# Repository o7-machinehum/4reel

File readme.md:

# 4reel
4reel is a platform for robots that don't have enough computing power to run machine vision algorithms. It's capable of stereo depth processing, image classification and SLAM.

When connected over USB-C the device will present itself as an Ethernet adapter and DHCP you an IP address, configuration can be done on the web portal at `http://192.168.77.1:8080/`

The JST connecter can be used to send data UART to an Arduino, ESP32, etc. The same JST conncetor can be used to power the device with 5V.

## System Overview

## Repo structure
``` bash
.
|-- img
|-- os
|-- readme.md
|-- ref
|-- rv1103    # Current tested board
|-- rv1106    # Next generation
`-- scripts   # Automation scripts I wrote
```

# Media
- https://youtube.com/shorts/XkLzl0wEfN4?si=KPXePSXCayTTsI1j

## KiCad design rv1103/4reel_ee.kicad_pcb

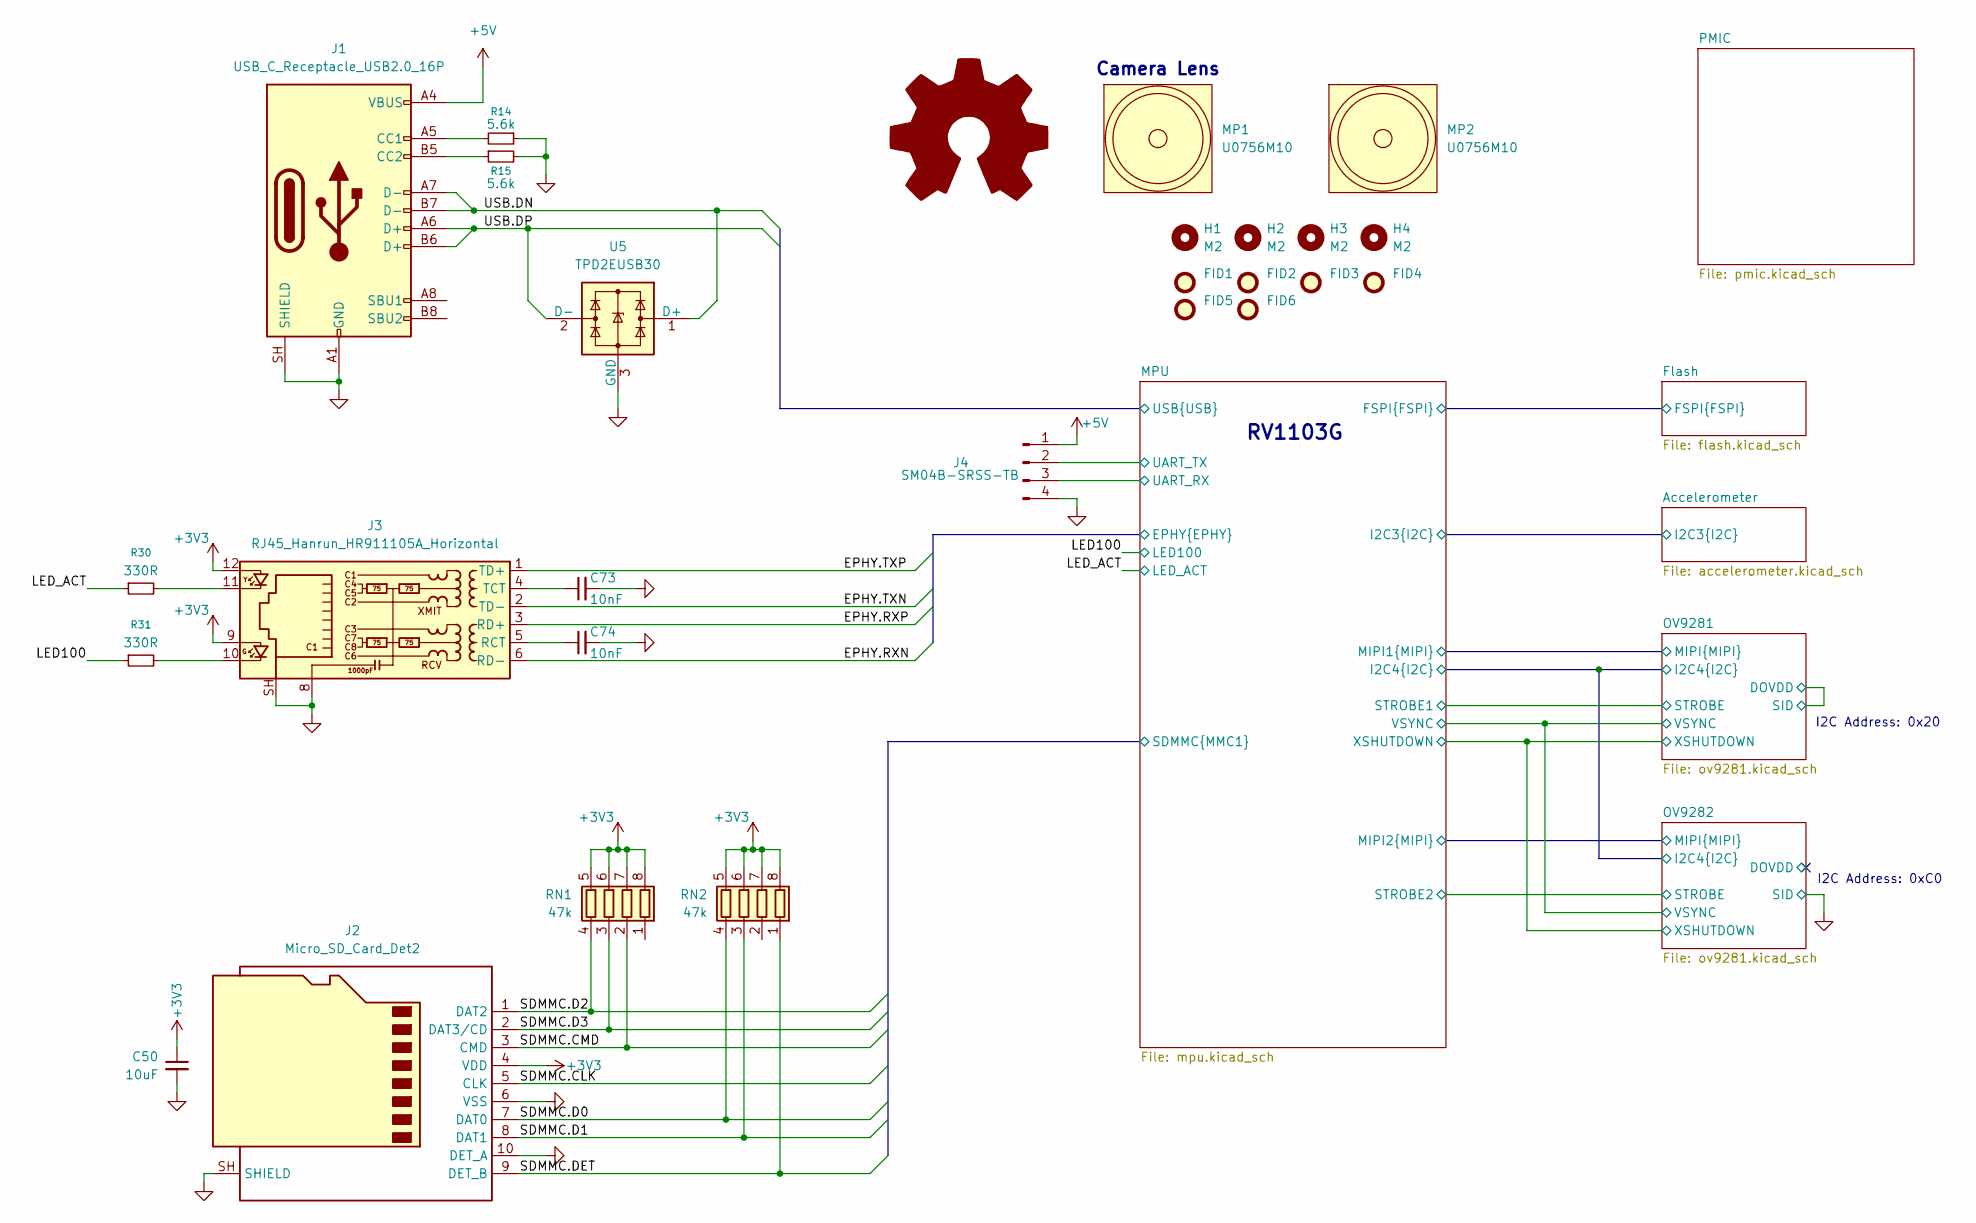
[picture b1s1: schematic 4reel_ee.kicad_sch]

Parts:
C50: 10uF; C_0402_1005Metric; MPN GRM155R60J106ME05D
C73, C74: 10nF; C_0402_1005Metric; MPN C0402C103K5REC7411
FID1, FID2, FID3, FID4, FID5, FID6: Fiducial; Fiducial_0.5mm_Mask1.5mm
H1, H2, H3, H4: M2; MountingHole_2.2mm_M2
J1: USB_C_Receptacle_USB2.0_16P; USB_C_Receptacle_GCT_USB4105-xx-A_16P_TopMnt_Horizontal; MPN USB4105-GF-A-120
J2: Micro_SD_Card_Det2; microSD_HC_Hirose_DM3AT-SF-PEJM5; MPN DM3AT-SF-PEJM5
J3: RJ45_Hanrun_HR911105A_Horizontal; MPN HR911105A
J4: SM04B-SRSS-TB; JST_SH_SM04B-SRSS-TB_1x04-1MP_P1.00mm_Horizontal; MPN SM04B-SRSS-TB
MP1, MP2: Camera_Lens_20mm; MPN U0756M10
R14, R15: 5.6k; R_0402_1005Metric; MPN RC0402FR-075K6L
R30, R31: 330R; R_0402_1005Metric; MPN RC0402FR-07330RL
RN1, RN2: 47k; R_Array_Concave_4x0402; MPN CAT10-473J4LF
SYM1: Logo_Open_Hardware_Large; OSHW-Logo2_14.6x12mm_SilkScreen
U5: TPD2EUSB30; Texas_DRT-3; MPN TPD2EUSB30ADRTR

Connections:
+3V3: C50.1, J2.4 (VDD), J3.9, J3.12, RN1.5 (R4.2), RN1.6 (R3.2), RN1.7 (R2.2), RN1.8 (R1.2), RN2.5 (R4.2), RN2.6 (R3.2), RN2.7 (R2.2), RN2.8 (R1.2); also elsewhere on the board
+5V: J1.A4 (VBUS), J1.A9 (VBUS), J1.B4 (VBUS), J1.B9 (VBUS), J4.1; also elsewhere on the board
/LED100: R31.1; also elsewhere on the board
/LED_ACT: R30.1; also elsewhere on the board
/MPU/EPHY.RXN: J3.6 (RD-); also elsewhere on the board
/MPU/EPHY.RXP: J3.3 (RD+); also elsewhere on the board
/MPU/EPHY.TXN: J3.2 (TD-); also elsewhere on the board
/MPU/EPHY.TXP: J3.1 (TD+); also elsewhere on the board
/MPU/SDMMC.CLK: J2.5 (CLK); also elsewhere on the board
/MPU/SDMMC.CMD: J2.3 (CMD), RN1.2 (R2.1); also elsewhere on the board
/MPU/SDMMC.D0: J2.7 (DAT0), RN2.4 (R4.1); also elsewhere on the board
/MPU/SDMMC.D1: J2.8 (DAT1), RN2.3 (R3.1); also elsewhere on the board
/MPU/SDMMC.D2: J2.1 (DAT2), RN1.4 (R4.1); also elsewhere on the board
/MPU/SDMMC.D3: J2.2 (DAT3/CD), RN1.3 (R3.1); also elsewhere on the board
/MPU/SDMMC.DET: J2.9 (DET_B), RN2.1 (R1.1); also elsewhere on the board
/MPU/UART_RX: J4.3; also elsewhere on the board
/MPU/UART_TX: J4.2; also elsewhere on the board
/MPU/USB.DN: J1.A7 (D-), J1.B7 (D-), U5.1 (D+); also elsewhere on the board
/MPU/USB.DP: J1.A6 (D+), J1.B6 (D+), U5.2 (D-); also elsewhere on the board
GND: C50.2, C73.2, C74.2, J1.A1 (GND), J1.A12 (GND), J1.B1 (GND), J1.B12 (GND), J1.SH (SHIELD), J2.6 (VSS), J2.10 (DET_A), J2.SH (SHIELD), J3.8, J3.SH, J4.4, R14.1, R15.2, U5.3 (GND); also elsewhere on the board
unnamed: J1.A5 (CC1), R14.2
unnamed: J1.B5 (CC2), R15.1
unnamed: J3.10, R31.2
unnamed: J3.11, R30.2
unnamed: C74.1, J3.5 (RCT)
unnamed: C73.1, J3.4 (TCT)

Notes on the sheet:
Camera Lens
I2C Address: 0x20
I2C Address: 0xC0
RV1103G

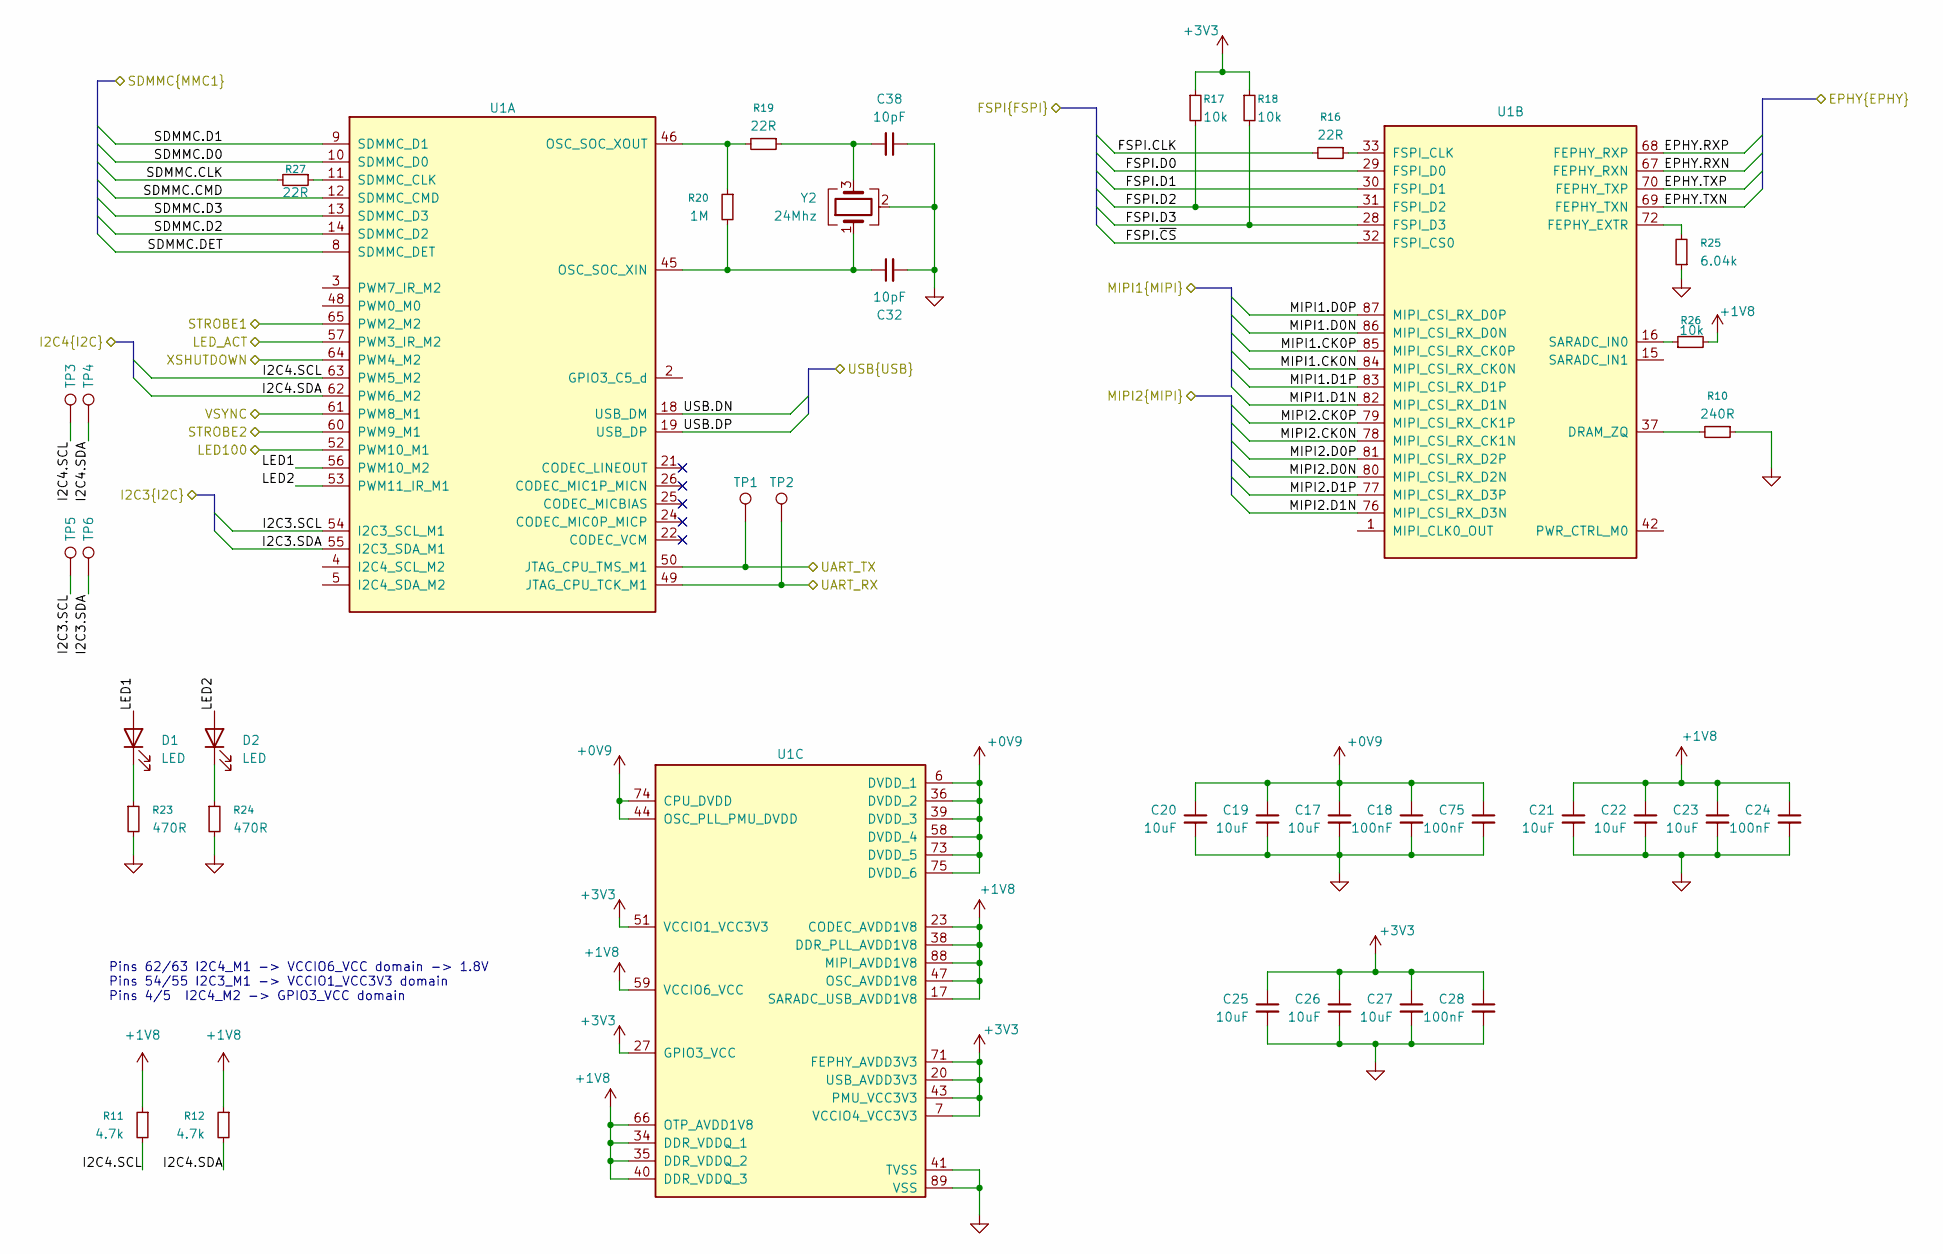
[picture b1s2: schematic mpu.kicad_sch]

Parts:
C17, C19, C20, C21, C22, C23, C25, C26, C27: 10uF; C_0402_1005Metric; MPN GRM155R60J106ME05D
C18, C24, C28, C75: 100nF; C_0402_1005Metric; MPN CL05B104KP5VPNC
C32, C38: 10pF; C_0402_1005Metric; MPN GCM1555C1H100JA16D
D1, D2: LED; LED_0402_1005Metric; MPN LTST-C281KGKT
R10: 240R; R_0402_1005Metric; MPN RC0402FR-07240RL
R11, R12: 4.7k; R_0402_1005Metric; MPN RC0402FR-074K7L
R16, R19: 22R; R_0402_1005Metric; MPN RC0402FR-0722RL
R17, R18, R26: 10k; R_0402_1005Metric; MPN RC0402FR-0710KL
R20: 1M; R_0402_1005Metric; MPN RC0402FR-071ML
R23, R24: 470R; R_0402_1005Metric; MPN RC0402FR-07470RL
R25: 6.04k; R_0402_1005Metric; MPN RC0402FR-076K04L
R27: 22R; R_0201_0603Metric; MPN RC0201FR-0722RL
TP1, TP2: TestPoint; TestPoint_Pad_1.5x1.5mm
TP3, TP4, TP5, TP6: TestPoint; TestPoint_Pad_1.0x1.0mm
U1: RV1103G; Rockchip_QFN-88-1EP_9x9mm_P0.35mm_EP6.5x6.5mm; MPN RV1103G1
Y2: 24Mhz; Crystal_SMD_2016-4Pin_2.0x1.6mm; MPN ECS-240-8-37B-CKY-TR

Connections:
+0V9: C17.1, C18.1, C19.1, C20.1, C75.1, U1.6 (DVDD_1), U1.36 (DVDD_2), U1.39 (DVDD_3), U1.44 (OSC_PLL_PMU_DVDD), U1.58 (DVDD_4), U1.73 (DVDD_5), U1.74 (CPU_DVDD), U1.75 (DVDD_6); also elsewhere on the board
+1V8: C21.1, C22.1, C23.1, C24.1, R11.1, R12.1, R26.2, U1.17 (SARADC_USB_AVDD1V8), U1.23 (CODEC_AVDD1V8), U1.34 (DDR_VDDQ_1), U1.35 (DDR_VDDQ_2), U1.38 (DDR_PLL_AVDD1V8), U1.40 (DDR_VDDQ_3), U1.47 (OSC_AVDD1V8), U1.59 (VCCIO6_VCC), U1.66 (OTP_AVDD1V8), U1.88 (MIPI_AVDD1V8); also elsewhere on the board
+3V3: C25.1, C26.1, C27.1, C28.1, R17.1, R18.1, U1.7 (VCCIO4_VCC3V3), U1.20 (USB_AVDD3V3), U1.27 (GPIO3_VCC), U1.43 (PMU_VCC3V3), U1.51 (VCCIO1_VCC3V3), U1.71 (FEPHY_AVDD3V3); also elsewhere on the board
/Accelerometer/I2C3.SCL: TP5.1 (1_1), U1.54 (I2C3_SCL_M1); also elsewhere on the board
/Accelerometer/I2C3.SDA: TP6.1 (1_1), U1.55 (I2C3_SDA_M1); also elsewhere on the board
/Flash/FSPI.CLK: R16.2; also elsewhere on the board
/Flash/FSPI.D0: U1.29 (FSPI_D0); also elsewhere on the board
/Flash/FSPI.D1: U1.30 (FSPI_D1); also elsewhere on the board
/Flash/FSPI.D2: R17.2, U1.31 (FSPI_D2); also elsewhere on the board
/Flash/FSPI.D3: R18.2, U1.28 (FSPI_D3); also elsewhere on the board
/Flash/FSPI.~CS: U1.32 (FSPI_CS0); also elsewhere on the board
/LED100: U1.52 (PWM10_M1); also elsewhere on the board
/LED_ACT: U1.57 (PWM3_IR_M2); also elsewhere on the board
/MPU/EPHY.RXN: U1.67 (FEPHY_RXN); also elsewhere on the board
/MPU/EPHY.RXP: U1.68 (FEPHY_RXP); also elsewhere on the board
/MPU/EPHY.TXN: U1.69 (FEPHY_TXN); also elsewhere on the board
/MPU/EPHY.TXP: U1.70 (FEPHY_TXP); also elsewhere on the board
/MPU/I2C4.SCL: R11.2, TP3.1 (1_1), U1.63 (PWM5_M2); also elsewhere on the board
/MPU/I2C4.SDA: R12.2, TP4.1 (1_1), U1.62 (PWM6_M2); also elsewhere on the board
/MPU/LED1: D1.2 (A), U1.56 (PWM10_M2)
/MPU/LED2: D2.2 (A), U1.53 (PWM11_IR_M1)
/MPU/MIPI1.CK0N: U1.84 (MIPI_CSI_RX_CK0N); also elsewhere on the board
/MPU/MIPI1.CK0P: U1.85 (MIPI_CSI_RX_CK0P); also elsewhere on the board
/MPU/MIPI1.D0N: U1.86 (MIPI_CSI_RX_D0N); also elsewhere on the board
/MPU/MIPI1.D0P: U1.87 (MIPI_CSI_RX_D0P); also elsewhere on the board
/MPU/MIPI1.D1N: U1.82 (MIPI_CSI_RX_D1N); also elsewhere on the board
/MPU/MIPI1.D1P: U1.83 (MIPI_CSI_RX_D1P); also elsewhere on the board
/MPU/MIPI2.CK0N: U1.78 (MIPI_CSI_RX_CK1N); also elsewhere on the board
/MPU/MIPI2.CK0P: U1.79 (MIPI_CSI_RX_CK1P); also elsewhere on the board
/MPU/MIPI2.D0N: U1.80 (MIPI_CSI_RX_D2N); also elsewhere on the board
/MPU/MIPI2.D0P: U1.81 (MIPI_CSI_RX_D2P); also elsewhere on the board
/MPU/MIPI2.D1N: U1.76 (MIPI_CSI_RX_D3N); also elsewhere on the board
/MPU/MIPI2.D1P: U1.77 (MIPI_CSI_RX_D3P); also elsewhere on the board
/MPU/SDMMC.CLK: R27.2; also elsewhere on the board
/MPU/SDMMC.CMD: U1.12 (SDMMC_CMD); also elsewhere on the board
/MPU/SDMMC.D0: U1.10 (SDMMC_D0); also elsewhere on the board
/MPU/SDMMC.D1: U1.9 (SDMMC_D1); also elsewhere on the board
/MPU/SDMMC.D2: U1.14 (SDMMC_D2); also elsewhere on the board
/MPU/SDMMC.D3: U1.13 (SDMMC_D3); also elsewhere on the board
/MPU/SDMMC.DET: U1.8 (SDMMC_DET); also elsewhere on the board
/MPU/STROBE1: U1.65 (PWM2_M2); also elsewhere on the board
/MPU/STROBE2: U1.60 (PWM9_M1); also elsewhere on the board
/MPU/UART_RX: TP2.1 (1_1), U1.49 (JTAG_CPU_TCK_M1); also elsewhere on the board
/MPU/UART_TX: TP1.1 (1_1), U1.50 (JTAG_CPU_TMS_M1); also elsewhere on the board
/MPU/USB.DN: U1.18 (USB_DM); also elsewhere on the board
/MPU/USB.DP: U1.19 (USB_DP); also elsewhere on the board
/MPU/VSYNC: U1.61 (PWM8_M1); also elsewhere on the board
/MPU/XSHUTDOWN: U1.64 (PWM4_M2); also elsewhere on the board
GND: C17.2, C18.2, C19.2, C20.2, C21.2, C22.2, C23.2, C24.2, C25.2, C26.2, C27.2, C28.2, C32.2, C38.1, C75.2, R10.1, R23.2, R24.2, R25.1, U1.41 (TVSS), U1.89 (VSS), Y2.2 (G), Y2.4 (G); also elsewhere on the board
unnamed: C38.2, R19.1, Y2.3
unnamed: D1.1 (K), R23.1
unnamed: D2.1 (K), R24.1
unnamed: R10.2, U1.37 (DRAM_ZQ)
unnamed: R25.2, U1.72 (FEPHY_EXTR)
unnamed: R16.1, U1.33 (FSPI_CLK)
unnamed: R26.1, U1.16 (SARADC_IN0)
unnamed: C32.1, R20.2, U1.45 (OSC_SOC_XIN), Y2.1
unnamed: R19.2, R20.1, U1.46 (OSC_SOC_XOUT)
unnamed: R27.1, U1.11 (SDMMC_CLK)

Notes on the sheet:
Pins 62/63 I2C4_M1 -> VCCIO6_VCC domain -> 1.8V Pins 54/55 I2C3_M1 -> VCCIO1_VCC3V3 domain Pins 4/5 I2C4_M2 -> GPIO3_VCC domain

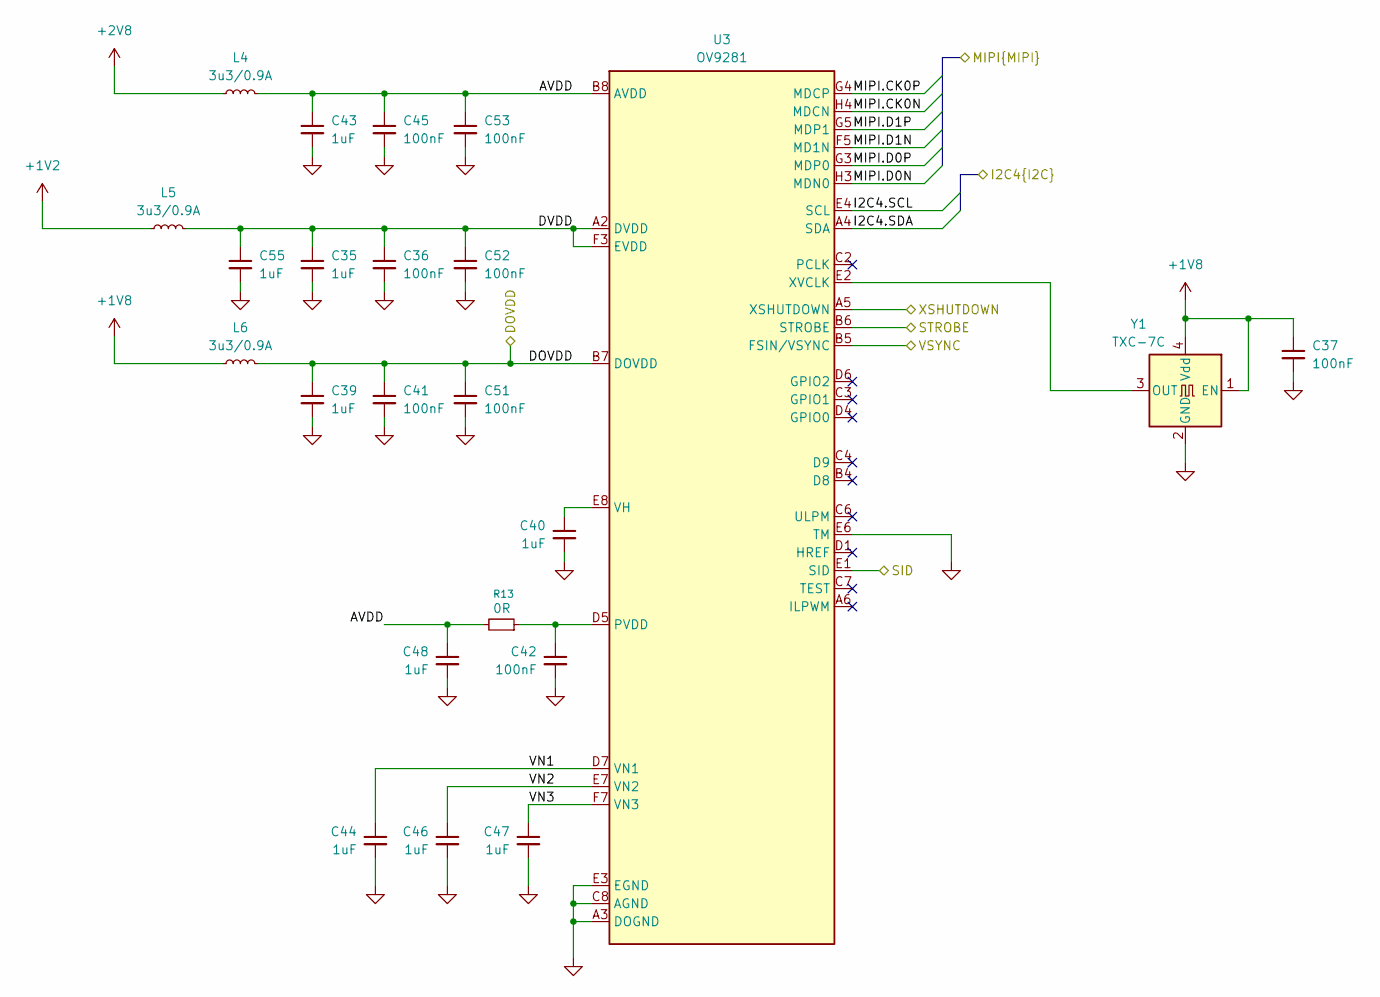
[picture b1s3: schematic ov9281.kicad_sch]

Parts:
C35, C39, C40, C43, C44, C46, C47, C48, C55: 1uF; C_0402_1005Metric; MPN C0402C105K9PACTU
C36, C37, C41, C42, C45, C51, C52, C53: 100nF; C_0402_1005Metric; MPN CL05B104KP5VPNC
L4, L5, L6: 3u3/0.9A; L_0805_2012Metric; MPN MLP2012S3R3MT0S1
R13: 0R; R_0402_1005Metric; MPN RC0402FR-070RL
U3: ImageSensor_OV9281; OV9281; MPN OV9281
Y1: TXC-7C; Oscillator_SMD_TXC_7C-4Pin_5.0x3.2mm; MPN SX5M24.000D20F30TNN

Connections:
+1V2: L5.1; also elsewhere on the board
+1V8: C37.1, L6.1, Y1.1 (EN), Y1.4 (Vdd); also elsewhere on the board
+2V8: L4.1; also elsewhere on the board
/MPU/I2C4.SCL: U3.E4 (SCL); also elsewhere on the board
/MPU/I2C4.SDA: U3.A4 (SDA); also elsewhere on the board
/MPU/MIPI1.CK0N: U3.H4 (MDCN); also elsewhere on the board
/MPU/MIPI1.CK0P: U3.G4 (MDCP); also elsewhere on the board
/MPU/MIPI1.D0N: U3.H3 (MDN0); also elsewhere on the board
/MPU/MIPI1.D0P: U3.G3 (MDP0); also elsewhere on the board
/MPU/MIPI1.D1N: U3.F5 (MD1N); also elsewhere on the board
/MPU/MIPI1.D1P: U3.G5 (MDP1); also elsewhere on the board
/MPU/STROBE1: U3.B6 (STROBE); also elsewhere on the board
/MPU/VSYNC: U3.B5 (FSIN/VSYNC); also elsewhere on the board
/MPU/XSHUTDOWN: U3.A5 (XSHUTDOWN); also elsewhere on the board
/OV9281/AVDD: C43.1, C45.1, C48.1, C53.1, L4.2, R13.2, U3.B8 (AVDD), U3.C1 (AVDD), U3.G7 (AVDD), U3.G8 (AVDD)
/OV9281/DOVDD: C39.1, C41.1, C51.1, L6.2, U3.B7 (DOVDD), U3.D3 (DOVDD), U3.E1 (SID), U3.H2 (DOVDD), U3.H6 (DOVDD)
/OV9281/DVDD: C35.1, C36.1, C52.1, C55.1, L5.2, U3.A2 (DVDD), U3.B1 (DVDD), U3.B3 (DVDD), U3.C5 (DVDD), U3.D8 (DVDD), U3.F2 (DVDD), U3.F3 (EVDD), U3.G1 (DVDD), U3.G6 (DVDD), U3.H5 (EVDD)
/OV9281/VN1: C44.1, U3.D7 (VN1)
/OV9281/VN2: C46.1, U3.E7 (VN2)
/OV9281/VN3: C47.1, U3.F7 (VN3)
GND: C35.2, C36.2, C37.2, C39.2, C40.2, C41.2, C42.2, C43.2, C44.2, C45.2, C46.2, C47.2, C48.2, C51.2, C52.2, C53.2, C55.2, U3.A3 (DOGND), U3.A7 (DOGND), U3.B2 (DOGND), U3.C8 (AGND), U3.D2 (AGND), U3.E3 (EGND), U3.E5 (EGND), U3.E6 (TM), U3.F1 (DOGND), U3.F4 (DOGND), U3.F6 (DOGND), U3.F8 (AGND), U3.G2 (DOGND), U3.H7 (AGND), Y1.2 (GND); also elsewhere on the board
unnamed: C42.1, R13.1, U3.D5 (PVDD)
unnamed: C40.1, U3.E8 (VH)
unnamed: U3.E2 (XVCLK), Y1.3 (OUT)

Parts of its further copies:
C56, C57, C58, C59, C60, C64, C65, C69, C71: 1uF; C_0402_1005Metric; MPN C0402C105K9PACTU
C61, C62, C63, C66, C67, C68, C70, C72: 100nF; C_0402_1005Metric; MPN CL05B104KP5VPNC
L7, L8, L9: 3u3/0.9A; L_0805_2012Metric; MPN MLP2012S3R3MT0S1
R32: 0R; R_0402_1005Metric; MPN RC0402FR-070RL
U9: ImageSensor_OV9281; OV9281; MPN OV9281
Y3: TXC-7C; Oscillator_SMD_TXC_7C-4Pin_5.0x3.2mm; MPN SX5M24.000D20F30TNN

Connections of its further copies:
+1V2: L7.1; also elsewhere on the board
+1V8: C72.1, L9.1, Y3.1 (EN), Y3.4 (Vdd); also elsewhere on the board
+2V8: L8.1; also elsewhere on the board
/MPU/I2C4.SCL: U9.E4 (SCL); also elsewhere on the board
/MPU/I2C4.SDA: U9.A4 (SDA); also elsewhere on the board
/MPU/MIPI2.CK0N: U9.H4 (MDCN); also elsewhere on the board
/MPU/MIPI2.CK0P: U9.G4 (MDCP); also elsewhere on the board
/MPU/MIPI2.D0N: U9.H3 (MDN0); also elsewhere on the board
/MPU/MIPI2.D0P: U9.G3 (MDP0); also elsewhere on the board
/MPU/MIPI2.D1N: U9.F5 (MD1N); also elsewhere on the board
/MPU/MIPI2.D1P: U9.G5 (MDP1); also elsewhere on the board
/MPU/STROBE2: U9.B6 (STROBE); also elsewhere on the board
/MPU/VSYNC: U9.B5 (FSIN/VSYNC); also elsewhere on the board
/MPU/XSHUTDOWN: U9.A5 (XSHUTDOWN); also elsewhere on the board
/OV9282/AVDD: C57.1, C61.1, C64.1, C66.1, L8.2, R32.2, U9.B8 (AVDD), U9.C1 (AVDD), U9.G7 (AVDD), U9.G8 (AVDD)
/OV9282/DOVDD: C59.1, C63.1, C68.1, L9.2, U9.B7 (DOVDD), U9.D3 (DOVDD), U9.H2 (DOVDD), U9.H6 (DOVDD)
/OV9282/DVDD: C56.1, C58.1, C62.1, C67.1, L7.2, U9.A2 (DVDD), U9.B1 (DVDD), U9.B3 (DVDD), U9.C5 (DVDD), U9.D8 (DVDD), U9.F2 (DVDD), U9.F3 (EVDD), U9.G1 (DVDD), U9.G6 (DVDD), U9.H5 (EVDD)
/OV9282/VN1: C60.1, U9.D7 (VN1)
/OV9282/VN2: C65.1, U9.E7 (VN2)
/OV9282/VN3: C69.1, U9.F7 (VN3)
GND: C56.2, C57.2, C58.2, C59.2, C60.2, C61.2, C62.2, C63.2, C64.2, C65.2, C66.2, C67.2, C68.2, C69.2, C70.2, C71.2, C72.2, U9.A3 (DOGND), U9.A7 (DOGND), U9.B2 (DOGND), U9.C8 (AGND), U9.D2 (AGND), U9.E1 (SID), U9.E3 (EGND), U9.E5 (EGND), U9.E6 (TM), U9.F1 (DOGND), U9.F4 (DOGND), U9.F6 (DOGND), U9.F8 (AGND), U9.G2 (DOGND), U9.H7 (AGND), Y3.2 (GND); also elsewhere on the board
unnamed: C70.1, R32.1, U9.D5 (PVDD)
unnamed: C71.1, U9.E8 (VH)
unnamed: U9.E2 (XVCLK), Y3.3 (OUT)

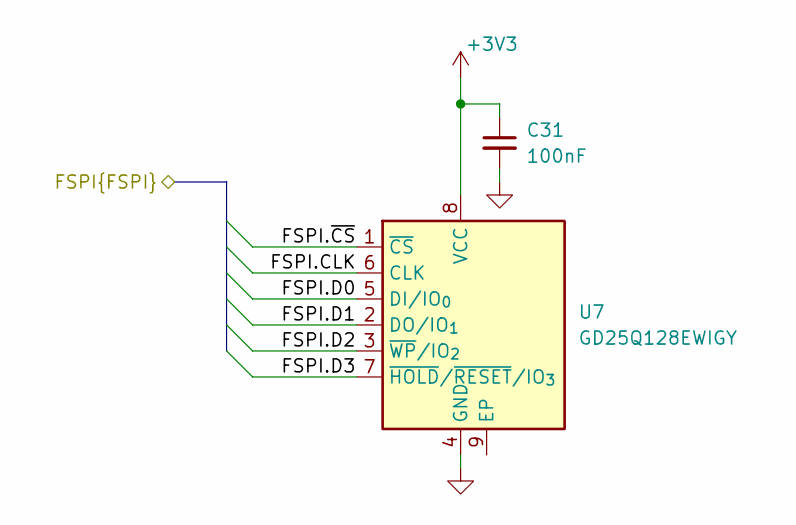
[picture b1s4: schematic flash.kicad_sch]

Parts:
C31: 100nF; C_0402_1005Metric; MPN CL05B104KP5VPNC
U7: GD25Q128EWIGY; WSON-8-1EP_6x5mm_P1.27mm_EP3.4x4.3mm; MPN GD25Q128EWIGY

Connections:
+3V3: C31.1, U7.8 (VCC); also elsewhere on the board
/Flash/FSPI.CLK: U7.6 (CLK); also elsewhere on the board
/Flash/FSPI.D0: U7.5 (DI/IO_{0}); also elsewhere on the board
/Flash/FSPI.D1: U7.2 (DO/IO_{1}); also elsewhere on the board
/Flash/FSPI.D2: U7.3 (~WP/IO_{2}); also elsewhere on the board
/Flash/FSPI.D3: U7.7 (~HOLD/~RESET/IO_{3}); also elsewhere on the board
/Flash/FSPI.~CS: U7.1 (~CS); also elsewhere on the board
GND: C31.2, U7.4 (GND); also elsewhere on the board

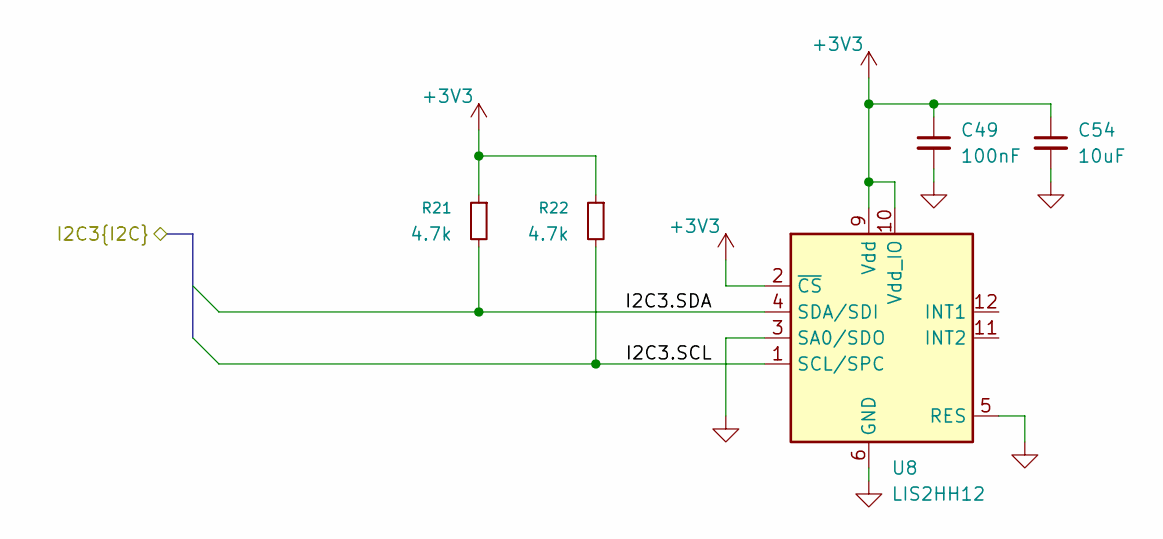
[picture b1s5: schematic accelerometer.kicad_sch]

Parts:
C49: 100nF; C_0402_1005Metric; MPN CL05B104KP5VPNC
C54: 10uF; C_0402_1005Metric; MPN GRM155R60J106ME05D
R21, R22: 4.7k; R_0402_1005Metric; MPN RC0402FR-074K7L
U8: LIS2HH12; LGA-12_2x2mm_P0.5mm; MPN LIS2HH12TR

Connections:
+3V3: C49.1, C54.1, R21.1, R22.1, U8.2 (~CS), U8.9 (Vdd), U8.10 (Vdd_IO); also elsewhere on the board
/Accelerometer/I2C3.SCL: R22.2, U8.1 (SCL/SPC); also elsewhere on the board
/Accelerometer/I2C3.SDA: R21.2, U8.4 (SDA/SDI); also elsewhere on the board
GND: C49.2, C54.2, U8.3 (SA0/SDO), U8.5 (RES), U8.6 (GND), U8.7 (GND), U8.8 (GND); also elsewhere on the board

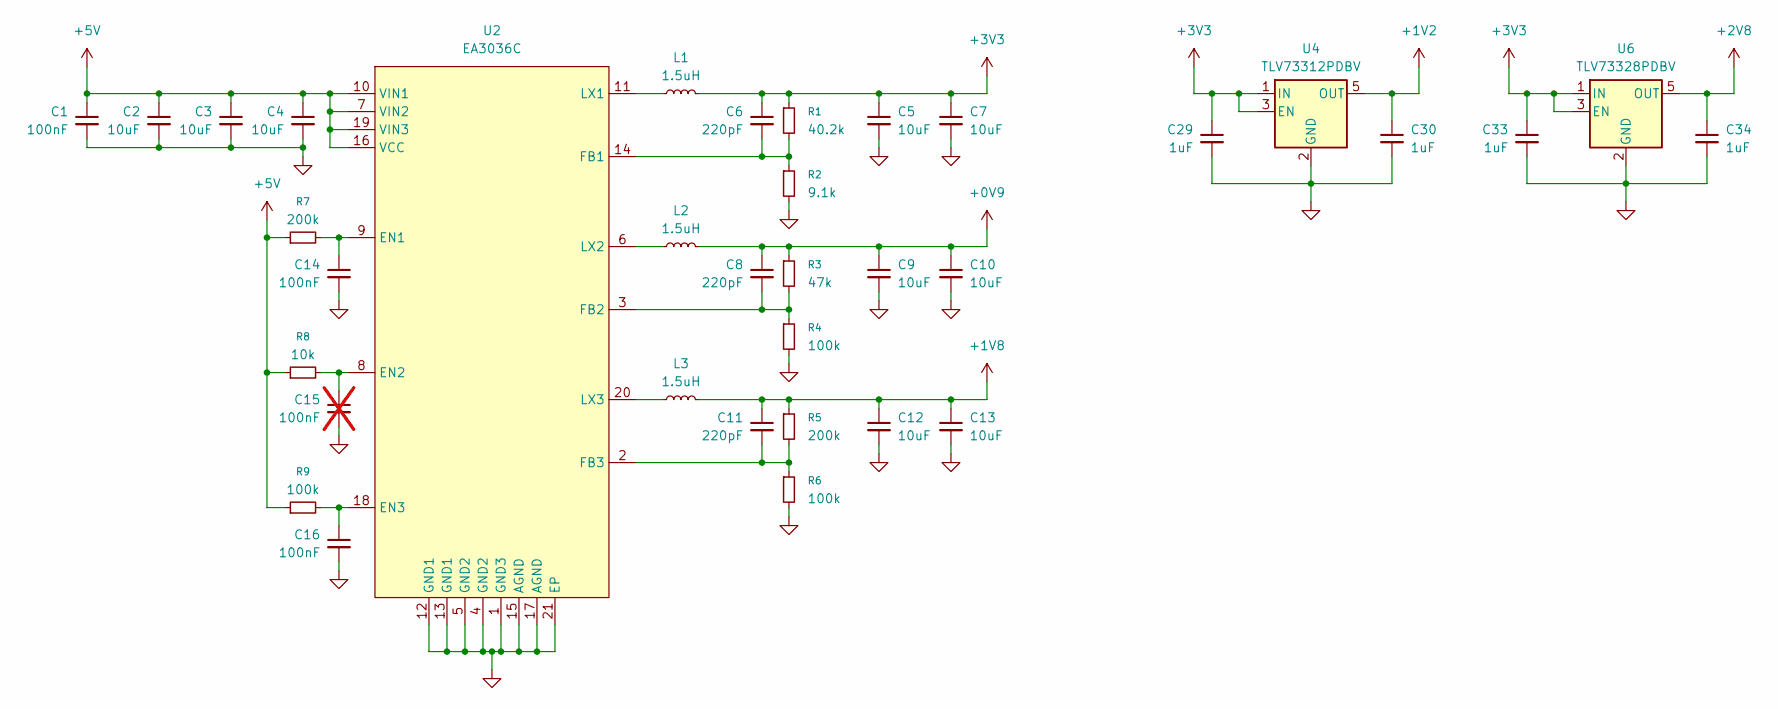
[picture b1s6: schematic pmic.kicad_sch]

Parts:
C1, C14, C16: 100nF; C_0402_1005Metric; MPN CL05B104KP5VPNC
C2, C3, C4, C5, C7, C9, C10, C12, C13: 10uF; C_0402_1005Metric; MPN GRM155R60J106ME05D
C6, C8, C11: 220pF; C_0402_1005Metric; MPN GCM1555C1H221JA16D
C15: 100nF; C_0402_1005Metric; MPN CL05B104KP5VPNC; not fitted
C29, C30, C33, C34: 1uF; C_0402_1005Metric; MPN C0402C105K9PACTU
L1, L2, L3: 1.5uH; L_1008_2520Metric; MPN DFE252012P-1R5M=P2
R1: 40.2k; R_0402_1005Metric; MPN RC0402FR-0740K2L
R2: 9.1k; R_0402_1005Metric; MPN RC0402FR-079K1L
R3: 47k; R_0402_1005Metric; MPN RC0402FR-0747KL
R4, R6, R9: 100k; R_0402_1005Metric; MPN RC0402FR-07100KL
R5, R7: 200k; R_0402_1005Metric; MPN RC0402FR-07200KL
R8: 10k; R_0402_1005Metric; MPN RC0402FR-0710KL
U2: EA3036C; QFN-20-1EP_3x3mm_P0.4mm_EP1.65x1.65mm; MPN EA3036CQBR
U4: TLV73312PDBV; SOT-23-5; MPN TLV73312PDBV
U6: TLV73328PDBV; SOT-23-5; MPN TLV73328PDBVR

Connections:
+0V9: C8.1, C9.1, C10.1, L2.2, R3.1; also elsewhere on the board
+1V2: C30.1, U4.5 (OUT); also elsewhere on the board
+1V8: C11.1, C12.1, C13.1, L3.2, R5.1; also elsewhere on the board
+2V8: C34.1, U6.5 (OUT); also elsewhere on the board
+3V3: C5.1, C6.1, C7.1, C29.1, C33.1, L1.2, R1.1, U4.1 (IN), U4.3 (EN), U6.1 (IN), U6.3 (EN); also elsewhere on the board
+5V: C1.1, C2.1, C3.1, C4.1, R7.1, R8.1, R9.1, U2.7 (VIN2), U2.10 (VIN1), U2.16 (VCC), U2.19 (VIN3); also elsewhere on the board
GND: C1.2, C2.2, C3.2, C4.2, C5.2, C7.2, C9.2, C10.2, C12.2, C13.2, C14.2, C15.2, C16.2, C29.2, C30.2, C33.2, C34.2, R2.2, R4.2, R6.2, U2.1 (GND3), U2.4 (GND2), U2.5 (GND2), U2.12 (GND1), U2.13 (GND1), U2.15 (AGND), U2.17 (AGND), U2.21 (EP), U4.2 (GND), U6.2 (GND); also elsewhere on the board
unnamed: C14.1, R7.2, U2.9 (EN1)
unnamed: C15.1, R8.2, U2.8 (EN2)
unnamed: C16.1, R9.2, U2.18 (EN3)
unnamed: C6.2, R1.2, R2.1, U2.14 (FB1)
unnamed: C8.2, R3.2, R4.1, U2.3 (FB2)
unnamed: C11.2, R5.2, R6.1, U2.2 (FB3)
unnamed: L1.1, U2.11 (LX1)
unnamed: L2.1, U2.6 (LX2)
unnamed: L3.1, U2.20 (LX3)

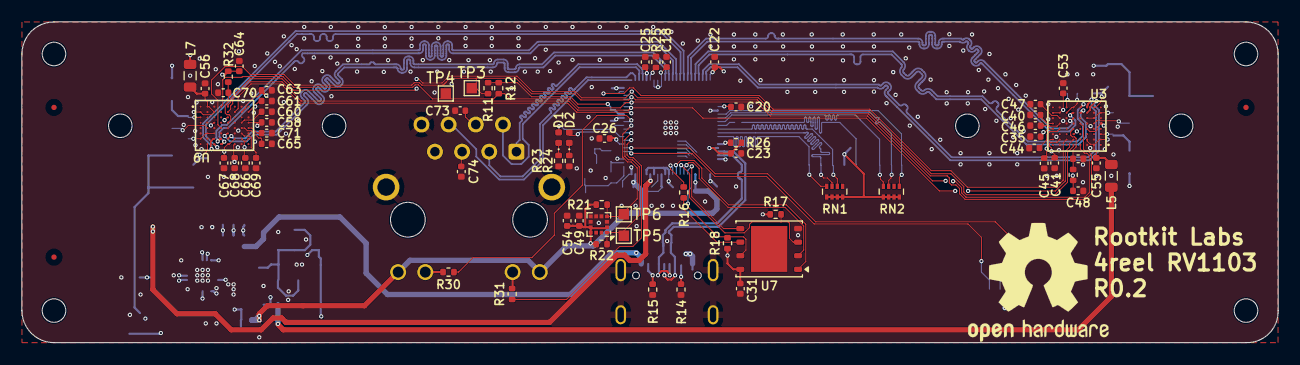
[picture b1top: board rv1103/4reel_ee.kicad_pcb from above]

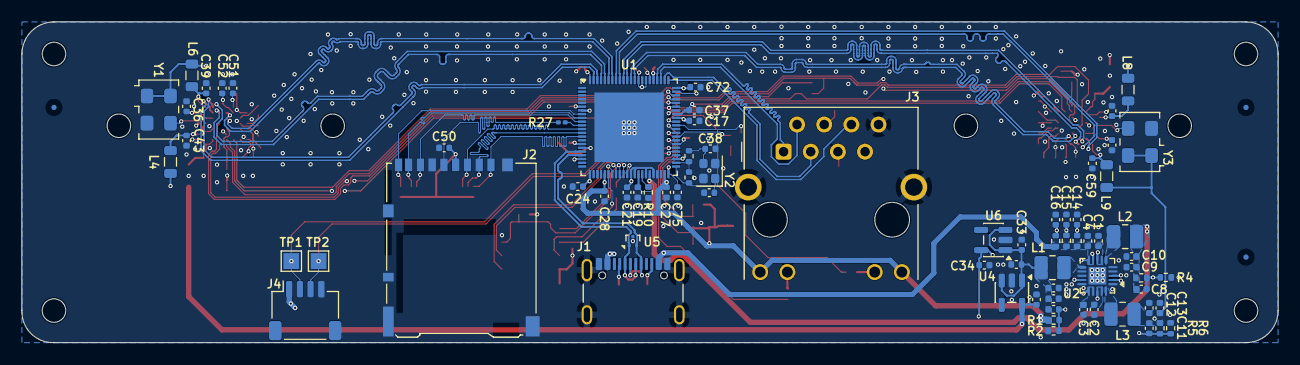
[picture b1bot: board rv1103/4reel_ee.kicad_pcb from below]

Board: 4 copper layers, 117.5 x 30.0 mm, 153 parts (77 on the bottom side), 95 nets.

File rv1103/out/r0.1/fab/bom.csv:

"Designator","Value","Footprint","Quantity","Part Number"
"C1,C14,C16,C18,C24,C28,C31,C36,C37,C41,C42,C45,C49,C51-C53,C61-C63,C66-C68,C70,C72,C75","100nF","Capacitor_SMD:C_0402_1005Metric","25","CL05B104KP5VPNC"
"C2-C5,C7,C9,C10,C12,C13,C17,C19-C23,C25-C27,C50,C54","10uF","Capacitor_SMD:C_0402_1005Metric","20","GRM155R60J106ME05D"
"C6,C8,C11","220pF","Capacitor_SMD:C_0402_1005Metric","3","GCM1555C1H221JA16D"
"C29,C30,C33-C35,C39,C40,C43,C44,C46-C48,C55-C60,C64,C65,C69,C71","1uF","Capacitor_SMD:C_0402_1005Metric","22","C0402C105K9PACTU"
"C32,C38","10pF","Capacitor_SMD:C_0402_1005Metric","2","GCM1555C1H100JA16D"
"C73,C74","10nF","Capacitor_SMD:C_0402_1005Metric","2","C0402C103K5REC7411"
"D1,D2","LED","LED_SMD:LED_0402_1005Metric","2","LTST-C281KGKT"
"J1","USB_C_Receptacle_USB2.0_16P","Connector_USB:USB_C_Receptacle_GCT_USB4105-xx-A_16P_TopMnt_Horizontal","1","USB4105-GF-A-120"
"J2","Micro_SD_Card_Det2","Connector_Card:microSD_HC_Hirose_DM3AT-SF-PEJM5","1","DM3AT-SF-PEJM5"
"J3","RJ45_Hanrun_HR911105A_Horizontal","Connector_RJ:RJ45_Hanrun_HR911105A_Horizontal","1","HR911105A"
"J4","JST","Connector_JST:JST_SH_SM04B-SRSS-TB_1x04-1MP_P1.00mm_Horizontal","1","SM04B-SRSS-TB"
"L1-L3","1.5uH","Inductor_SMD:L_1008_2520Metric","3","DFE252012P-1R5M=P2"
"L4-L9","3u3/0.9A","Inductor_SMD:L_0805_2012Metric","6","MLP2012S3R3MT0S1"
"R1","40.2k","Resistor_SMD:R_0402_1005Metric","1","RC0402FR-0740K2L"
"R2","9.1k","Resistor_SMD:R_0402_1005Metric","1","RC0402FR-079K1L"
"R3","47k","Resistor_SMD:R_0402_1005Metric","1","RC0402FR-0747KL"
"R4,R6,R9","100k","Resistor_SMD:R_0402_1005Metric","3","RC0402FR-07100KL"
"R5,R7","200k","Resistor_SMD:R_0402_1005Metric","2","RC0402FR-07200KL"
"R8,R17,R18,R26","10k","Resistor_SMD:R_0402_1005Metric","4","RC0402FR-0710KL"
"R10","240R","Resistor_SMD:R_0402_1005Metric","1","RC0402FR-07240RL"
"R11,R12,R21,R22","4.7k","Resistor_SMD:R_0402_1005Metric","4","RC0402FR-074K7L"
"R13,R32","0R","Resistor_SMD:R_0402_1005Metric","2","RC0402FR-070RL"
"R14,R15","5.6k","Resistor_SMD:R_0402_1005Metric","2","RC0402FR-075K6L"
"R16,R19","22R","Resistor_SMD:R_0402_1005Metric","2","RC0402FR-0722RL"
"R20","1M","Resistor_SMD:R_0402_1005Metric","1","RC0402FR-071ML"
"R23,R24","1k","Resistor_SMD:R_0402_1005Metric","2","RC0402FR-071KL"
"R25","6.04k","Resistor_SMD:R_0402_1005Metric","1","RC0402FR-076K04L"
"R27","22R","Resistor_SMD:R_0201_0603Metric","1","RC0201FR-0722RL"
"R30,R31","330R","Resistor_SMD:R_0402_1005Metric","2","RC0402FR-07330RL"
"RN1,RN2","47k","Resistor_SMD:R_Array_Concave_4x0402","2","CAT10-473J4LF"
"TP3-TP6","TestPoint","TestPoint:TestPoint_Pad_1.0x1.0mm","4",""
"U1","RV1103G","rv1103b:Rockchip_QFN-88-1EP_9x9mm_P0.35mm_EP6.5x6.5mm","1","RV1103BG3"
"U2","EA3036C","Package_DFN_QFN:QFN-20-1EP_3x3mm_P0.4mm_EP1.65x1.65mm","1","EA3036CQBR"
"U3,U9","ImageSensor_OV9281","ov9281:OV9281","2","OV9281"
"U4","TLV73312PDBV","Package_TO_SOT_SMD:SOT-23-5","1","TLV73312PDBV"
"U5","TPD2EUSB30","Package_TO_SOT_SMD:Texas_DRT-3","1","TPD2EUSB30ADRTR"
"U6","TLV73328PDBV","Package_TO_SOT_SMD:SOT-23-5","1","TLV73328PDBVR"
"U7","W25Q32JVZP","Package_SON:WSON-8-1EP_6x5mm_P1.27mm_EP3.4x4.3mm","1","W25Q32JVZPIQ"
"U8","LIS2HH12","Package_LGA:LGA-12_2x2mm_P0.5mm","1","LIS2HH12TR"
"Y1,Y3","TXC-7C","Oscillator:Oscillator_SMD_TXC_7C-4Pin_5.0x3.2mm","2","SX5M24.000D20F30TNN"
"Y2","24Mhz","Crystal:Crystal_SMD_2016-4Pin_2.0x1.6mm","1","ECS-240-8-37B-CKY-TR"

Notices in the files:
parts and their libraries:
License: Apache-2.0
